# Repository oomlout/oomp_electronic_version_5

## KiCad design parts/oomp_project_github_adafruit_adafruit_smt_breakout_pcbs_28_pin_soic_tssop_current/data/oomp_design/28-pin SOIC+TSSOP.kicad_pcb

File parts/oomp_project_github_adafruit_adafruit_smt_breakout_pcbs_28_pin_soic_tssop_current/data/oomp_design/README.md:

# OOMP KiCad design copy

Open `28-pin SOIC+TSSOP.kicad_pro` (or the `.kicad_pcb` / `.kicad_sch`) in KiCad. Local OOMP libraries are under `libraries/`. Original inputs are preserved in [../original/](../original/).

Only verified unchanged installed KiCad defaults were renamed. Modified, custom, unmatched and unavailable items remain unchanged. Soldering variants are never swapped during conversion. Existing pad coordinates, nets and UUIDs are preserved.

See [conversion_report.yaml](conversion_report.yaml) for every conversion and skip. Copy this directory before editing; regeneration refuses to overwrite edited design files.

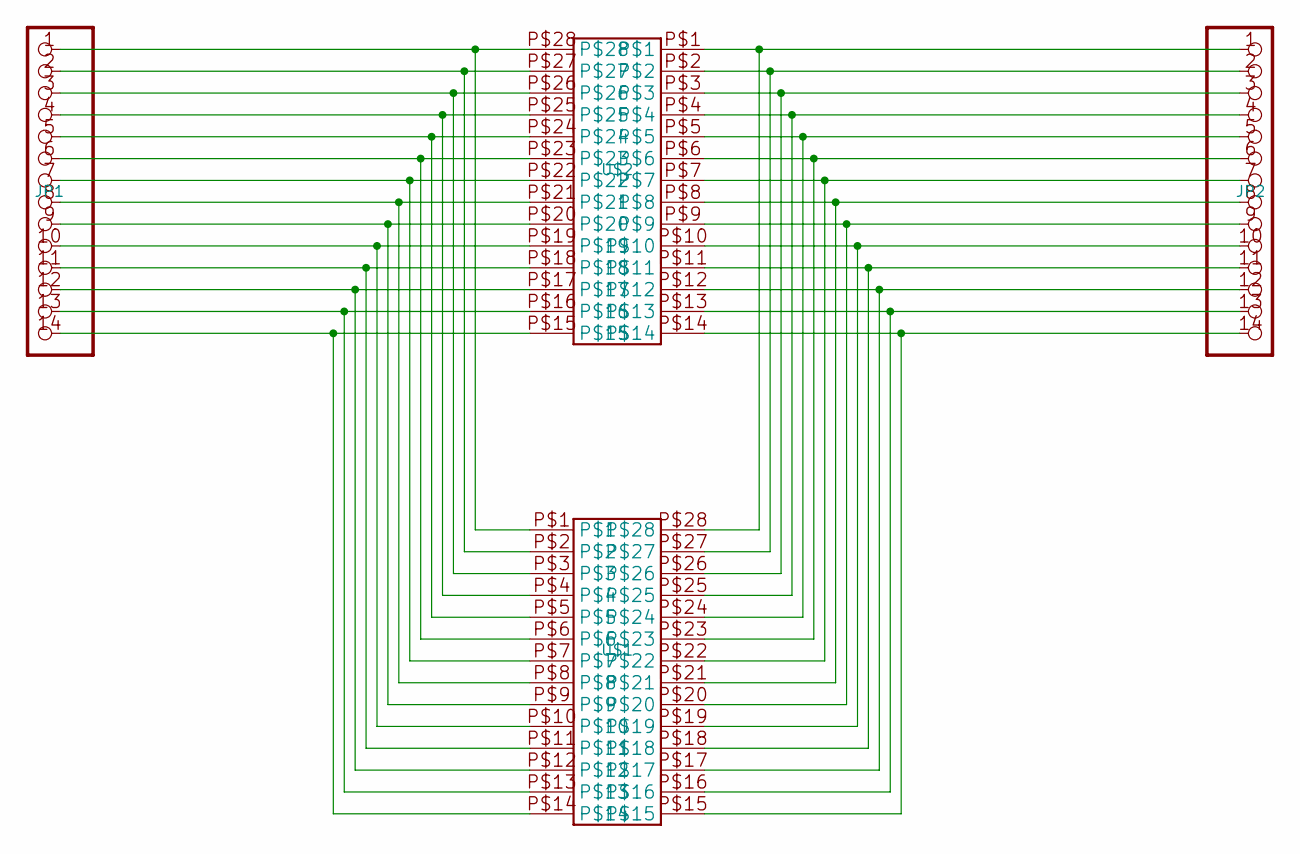
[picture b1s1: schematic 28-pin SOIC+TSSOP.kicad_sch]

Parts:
JP1, JP2: PADS-14
U$1: 28-PINSOIC-NW; SO28-NW
U$2: 28-PINTSSOP-NW; TSSOP28-NW

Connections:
unnamed: JP1.1, U$1.P$1, U$2.P$28
unnamed: JP1.2, U$1.P$2, U$2.P$27
unnamed: JP1.3, U$1.P$3, U$2.P$26
unnamed: JP1.4, U$1.P$4, U$2.P$25
unnamed: JP1.5, U$1.P$5, U$2.P$24
unnamed: JP1.6, U$1.P$6, U$2.P$23
unnamed: JP1.7, U$1.P$7, U$2.P$22
unnamed: JP1.8, U$1.P$8, U$2.P$21
unnamed: JP1.9, U$1.P$9, U$2.P$20
unnamed: JP1.10, U$1.P$10, U$2.P$19
unnamed: JP1.11, U$1.P$11, U$2.P$18
unnamed: JP1.12, U$1.P$12, U$2.P$17
unnamed: JP1.14, U$1.P$14, U$2.P$15
unnamed: JP2.1, U$1.P$28, U$2.P$1
unnamed: JP2.2, U$1.P$27, U$2.P$2
unnamed: JP2.3, U$1.P$26, U$2.P$3
unnamed: JP2.4, U$1.P$25, U$2.P$4
unnamed: JP2.5, U$1.P$24, U$2.P$5
unnamed: JP2.6, U$1.P$23, U$2.P$6
unnamed: JP2.7, U$1.P$22, U$2.P$7
unnamed: JP2.8, U$1.P$21, U$2.P$8
unnamed: JP2.9, U$1.P$20, U$2.P$9
unnamed: JP2.10, U$1.P$19, U$2.P$10
unnamed: JP2.11, U$1.P$18, U$2.P$11
unnamed: JP2.12, U$1.P$17, U$2.P$12
unnamed: JP2.13, U$1.P$16, U$2.P$13
unnamed: JP2.14, U$1.P$15, U$2.P$14
unnamed: JP1.13, U$1.P$13, U$2.P$16

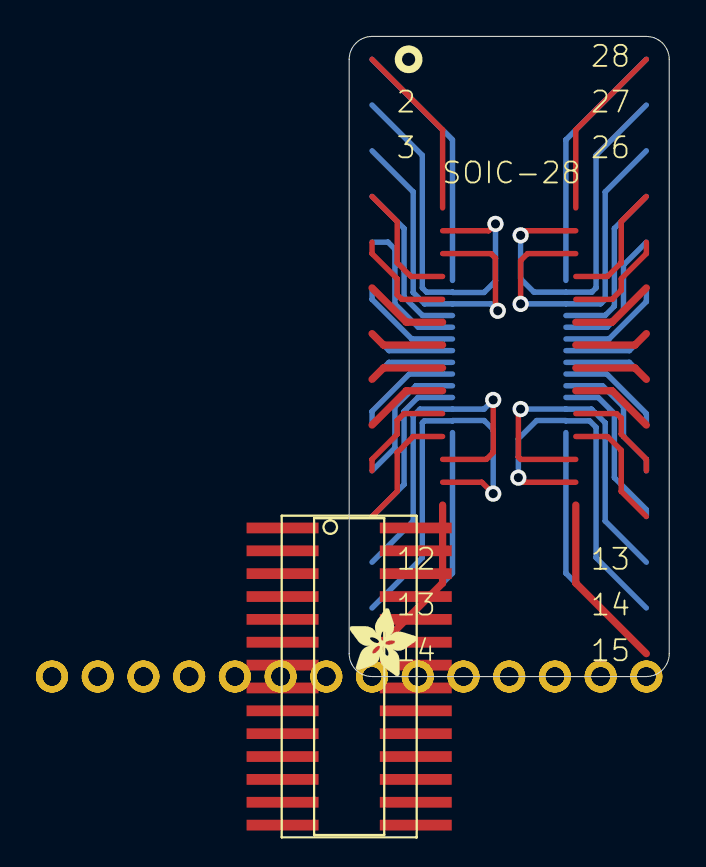
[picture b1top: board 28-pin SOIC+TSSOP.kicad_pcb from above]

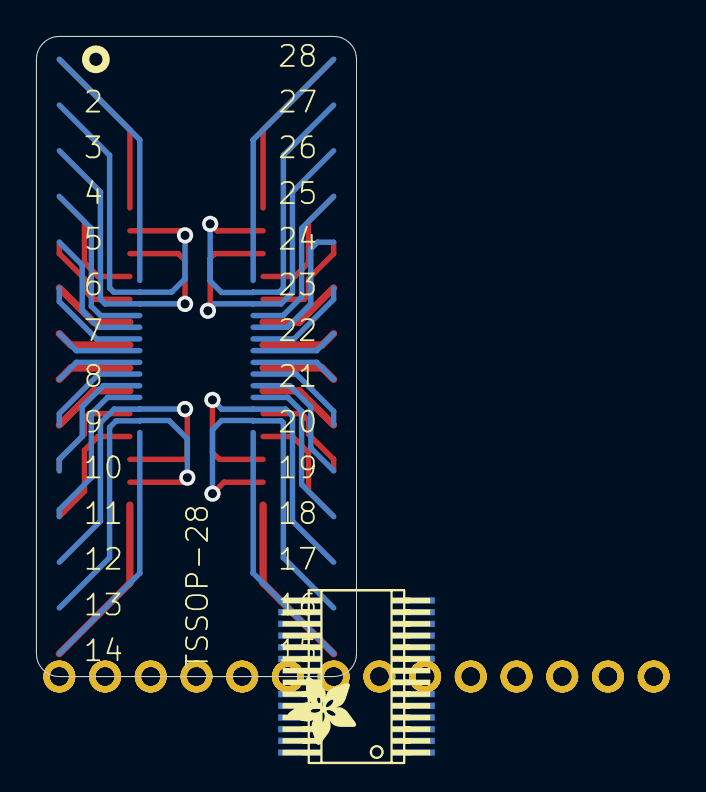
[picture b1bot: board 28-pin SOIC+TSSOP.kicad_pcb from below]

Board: 2 copper layers, 17.8 x 35.6 mm, 6 parts (2 on the bottom side), 28 nets.

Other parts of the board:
U$3, U$4: ADAFRUIT_3.5MM

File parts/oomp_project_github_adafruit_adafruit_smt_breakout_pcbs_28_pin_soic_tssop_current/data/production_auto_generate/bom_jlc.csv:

Comment,Designator,Footprint,LCSC Part #
,"U$3,U$4",28-pin SOIC+TSSOP-import-fps:ADAFRUIT_3.5MM,
,"JP1,JP2",28-pin SOIC+TSSOP-import-fps:PADS-14,
28-PINSOIC-NW,U$1,28-pin SOIC+TSSOP-import-fps:SO28-NW,
28-PINTSSOP-NW,U$2,28-pin SOIC+TSSOP-import-fps:TSSOP28-NW,

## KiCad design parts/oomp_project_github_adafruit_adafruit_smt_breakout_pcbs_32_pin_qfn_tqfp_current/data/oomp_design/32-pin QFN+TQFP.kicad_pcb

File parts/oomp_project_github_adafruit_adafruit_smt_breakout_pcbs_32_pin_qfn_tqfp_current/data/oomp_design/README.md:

# OOMP KiCad design copy

Open `32-pin QFN+TQFP.kicad_pro` (or the `.kicad_pcb` / `.kicad_sch`) in KiCad. Local OOMP libraries are under `libraries/`. Original inputs are preserved in [../original/](../original/).

Only verified unchanged installed KiCad defaults were renamed. Modified, custom, unmatched and unavailable items remain unchanged. Soldering variants are never swapped during conversion. Existing pad coordinates, nets and UUIDs are preserved.

See [conversion_report.yaml](conversion_report.yaml) for every conversion and skip. Copy this directory before editing; regeneration refuses to overwrite edited design files.

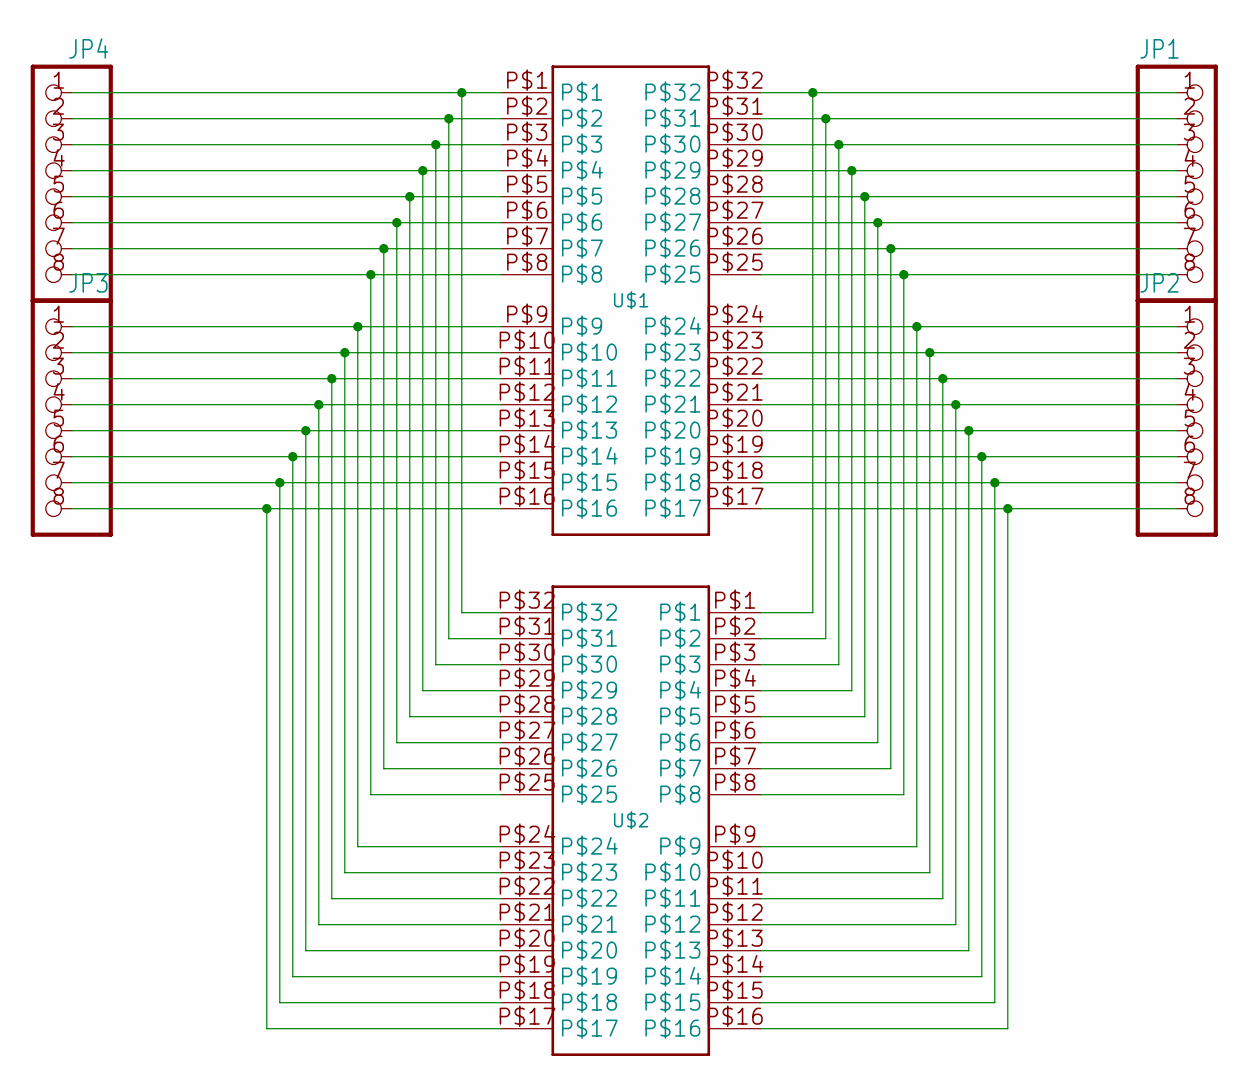
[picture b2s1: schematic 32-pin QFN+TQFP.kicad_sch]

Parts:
JP1, JP2, JP3, JP4: PADS-8CLEANBIG; PADS-8
U$1: 32-PINQFN; QFN32
U$2: 32-PINTQFP; TQFP32-08

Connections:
unnamed: JP4.1, U$1.P$1, U$2.P$32
unnamed: JP4.2, U$1.P$2, U$2.P$31
unnamed: JP4.3, U$1.P$3, U$2.P$30
unnamed: JP4.4, U$1.P$4, U$2.P$29
unnamed: JP4.5, U$1.P$5, U$2.P$28
unnamed: JP4.6, U$1.P$6, U$2.P$27
unnamed: JP4.7, U$1.P$7, U$2.P$26
unnamed: JP4.8, U$1.P$8, U$2.P$25
unnamed: JP3.1, U$1.P$9, U$2.P$24
unnamed: JP3.2, U$1.P$10, U$2.P$23
unnamed: JP3.3, U$1.P$11, U$2.P$22
unnamed: JP3.4, U$1.P$12, U$2.P$21
unnamed: JP3.5, U$1.P$13, U$2.P$20
unnamed: JP3.6, U$1.P$14, U$2.P$19
unnamed: JP3.7, U$1.P$15, U$2.P$18
unnamed: JP3.8, U$1.P$16, U$2.P$17
unnamed: JP1.1, U$1.P$32, U$2.P$1
unnamed: JP1.2, U$1.P$31, U$2.P$2
unnamed: JP1.3, U$1.P$30, U$2.P$3
unnamed: JP1.4, U$1.P$29, U$2.P$4
unnamed: JP1.5, U$1.P$28, U$2.P$5
unnamed: JP1.6, U$1.P$27, U$2.P$6
unnamed: JP1.7, U$1.P$26, U$2.P$7
unnamed: JP1.8, U$1.P$25, U$2.P$8
unnamed: JP2.1, U$1.P$24, U$2.P$9
unnamed: JP2.2, U$1.P$23, U$2.P$10
unnamed: JP2.3, U$1.P$22, U$2.P$11
unnamed: JP2.4, U$1.P$21, U$2.P$12
unnamed: JP2.5, U$1.P$20, U$2.P$13
unnamed: JP2.6, U$1.P$19, U$2.P$14
unnamed: JP2.7, U$1.P$18, U$2.P$15
unnamed: JP2.8, U$1.P$17, U$2.P$16

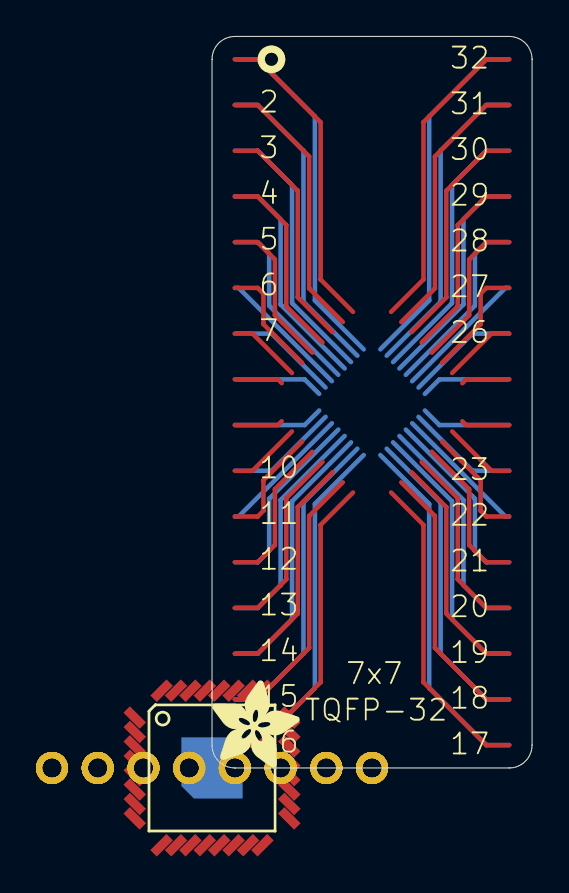
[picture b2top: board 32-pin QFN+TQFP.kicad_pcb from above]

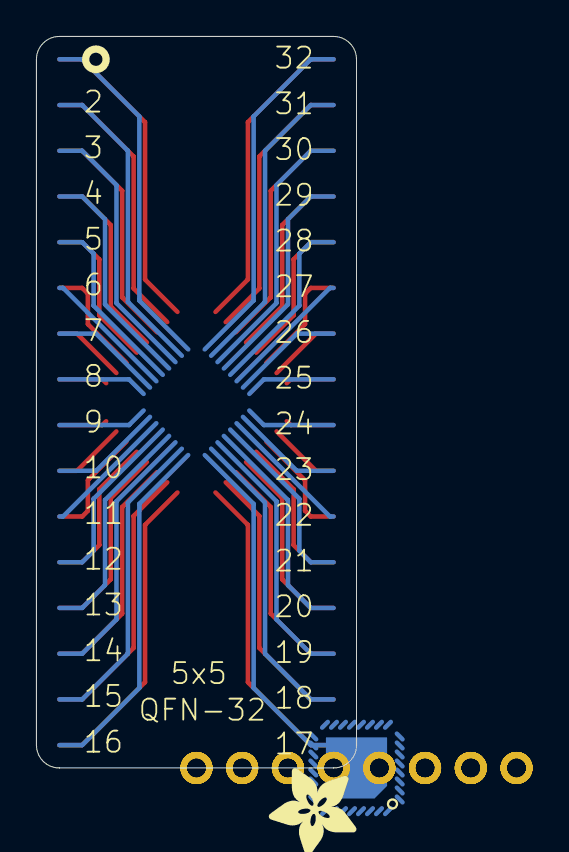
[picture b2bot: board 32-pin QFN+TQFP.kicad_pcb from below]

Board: 16 copper layers, 17.8 x 40.6 mm, 8 parts (2 on the bottom side), 32 nets.

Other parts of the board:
U$3, U$4: ADAFRUIT_5MM

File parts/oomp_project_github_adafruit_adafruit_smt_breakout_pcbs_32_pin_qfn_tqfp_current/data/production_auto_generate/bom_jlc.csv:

Comment,Designator,Footprint,LCSC Part #
,"U$3,U$4",32-pin QFN+TQFP-import-fps:ADAFRUIT_5MM,
,"JP1,JP2,JP3,JP4",32-pin QFN+TQFP-import-fps:PADS-8,
32-PINQFN,U$1,32-pin QFN+TQFP-import-fps:QFN32,
32-PINTQFP,U$2,32-pin QFN+TQFP-import-fps:TQFP32-08,

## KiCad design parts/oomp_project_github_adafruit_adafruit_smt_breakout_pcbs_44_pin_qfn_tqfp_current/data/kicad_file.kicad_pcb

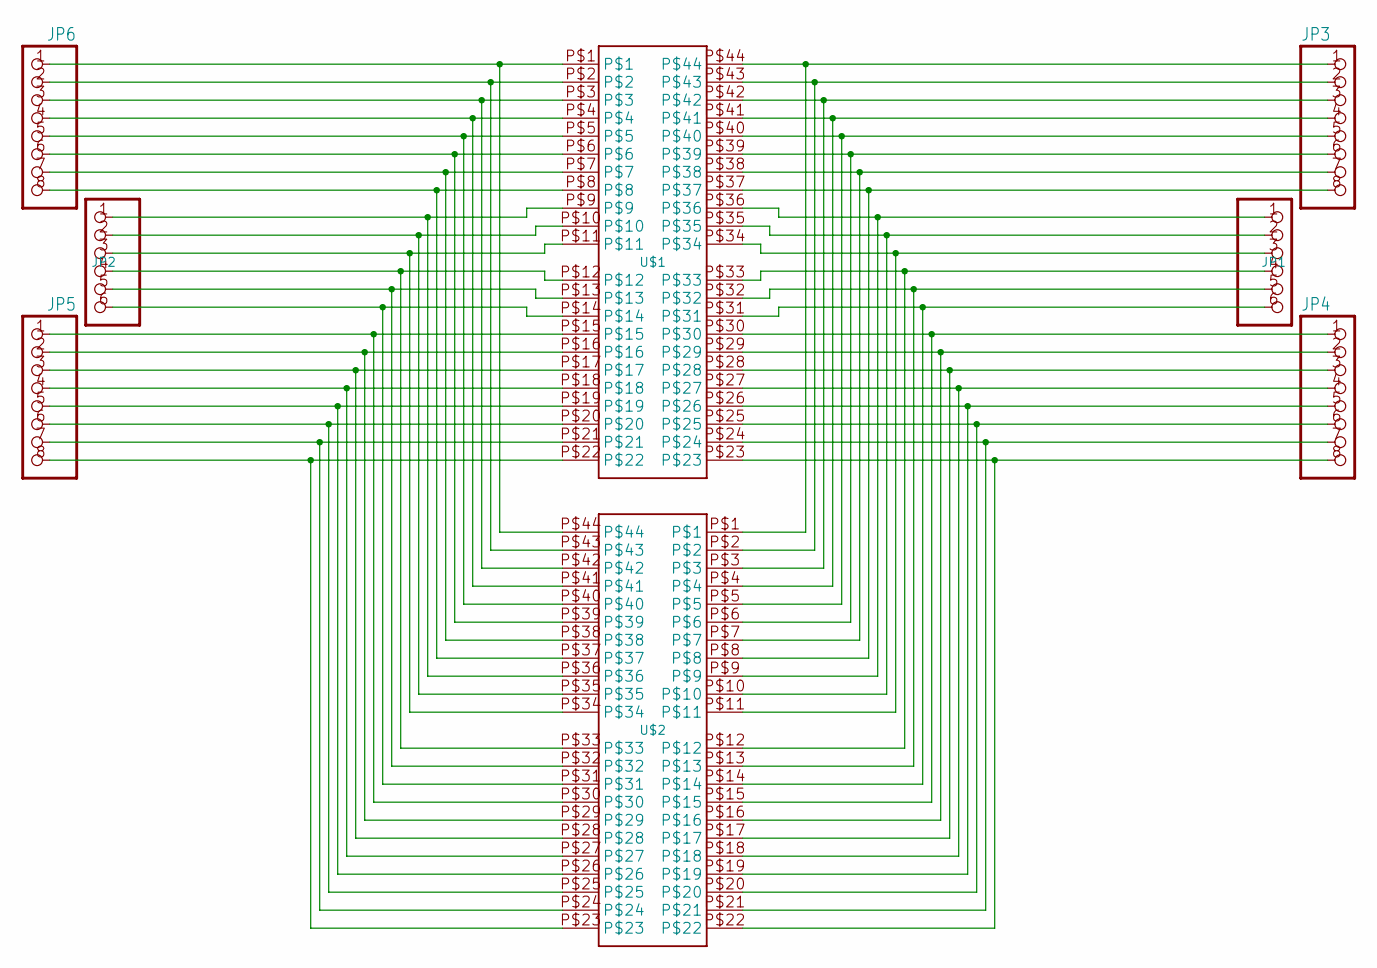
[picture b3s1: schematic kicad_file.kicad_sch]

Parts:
JP1, JP2: PADS-6
JP3, JP4, JP5, JP6: PADS-8CLEANBIG; PADS-8
U$1: 44-PINQFN; QFN44
U$2: 44-PINTQFP; TQFP44

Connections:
unnamed: JP6.1, U$1.P$1, U$2.P$44
unnamed: JP6.2, U$1.P$2, U$2.P$43
unnamed: JP6.3, U$1.P$3, U$2.P$42
unnamed: JP6.4, U$1.P$4, U$2.P$41
unnamed: JP6.5, U$1.P$5, U$2.P$40
unnamed: JP6.6, U$1.P$6, U$2.P$39
unnamed: JP6.7, U$1.P$7, U$2.P$38
unnamed: JP6.8, U$1.P$8, U$2.P$37
unnamed: JP5.1, U$1.P$15, U$2.P$30
unnamed: JP5.2, U$1.P$16, U$2.P$29
unnamed: JP5.3, U$1.P$17, U$2.P$28
unnamed: JP5.4, U$1.P$18, U$2.P$27
unnamed: JP5.5, U$1.P$19, U$2.P$26
unnamed: JP5.6, U$1.P$20, U$2.P$25
unnamed: JP5.7, U$1.P$21, U$2.P$24
unnamed: JP5.8, U$1.P$22, U$2.P$23
unnamed: JP4.1, U$1.P$30, U$2.P$15
unnamed: JP4.2, U$1.P$29, U$2.P$16
unnamed: JP4.3, U$1.P$28, U$2.P$17
unnamed: JP4.4, U$1.P$27, U$2.P$18
unnamed: JP4.5, U$1.P$26, U$2.P$19
unnamed: JP4.6, U$1.P$25, U$2.P$20
unnamed: JP4.7, U$1.P$24, U$2.P$21
unnamed: JP4.8, U$1.P$23, U$2.P$22
unnamed: JP3.1, U$1.P$44, U$2.P$1
unnamed: JP3.2, U$1.P$43, U$2.P$2
unnamed: JP3.3, U$1.P$42, U$2.P$3
unnamed: JP3.4, U$1.P$41, U$2.P$4
unnamed: JP3.5, U$1.P$40, U$2.P$5
unnamed: JP3.6, U$1.P$39, U$2.P$6
unnamed: JP3.7, U$1.P$38, U$2.P$7
unnamed: JP3.8, U$1.P$37, U$2.P$8
unnamed: JP1.4, U$1.P$33, U$2.P$12
unnamed: JP1.5, U$1.P$32, U$2.P$13
unnamed: JP1.6, U$1.P$31, U$2.P$14
unnamed: JP1.3, U$1.P$34, U$2.P$11
unnamed: JP1.2, U$1.P$35, U$2.P$10
unnamed: JP1.1, U$1.P$36, U$2.P$9
unnamed: JP2.3, U$1.P$11, U$2.P$34
unnamed: JP2.2, U$1.P$10, U$2.P$35
unnamed: JP2.1, U$1.P$9, U$2.P$36
unnamed: JP2.4, U$1.P$12, U$2.P$33
unnamed: JP2.5, U$1.P$13, U$2.P$32
unnamed: JP2.6, U$1.P$14, U$2.P$31

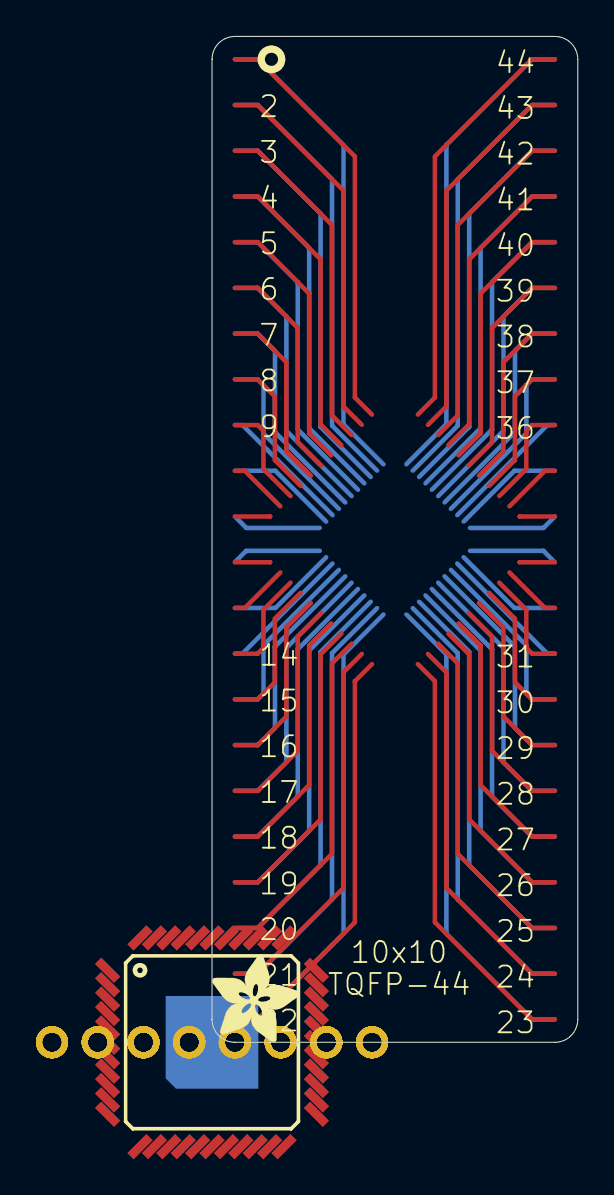
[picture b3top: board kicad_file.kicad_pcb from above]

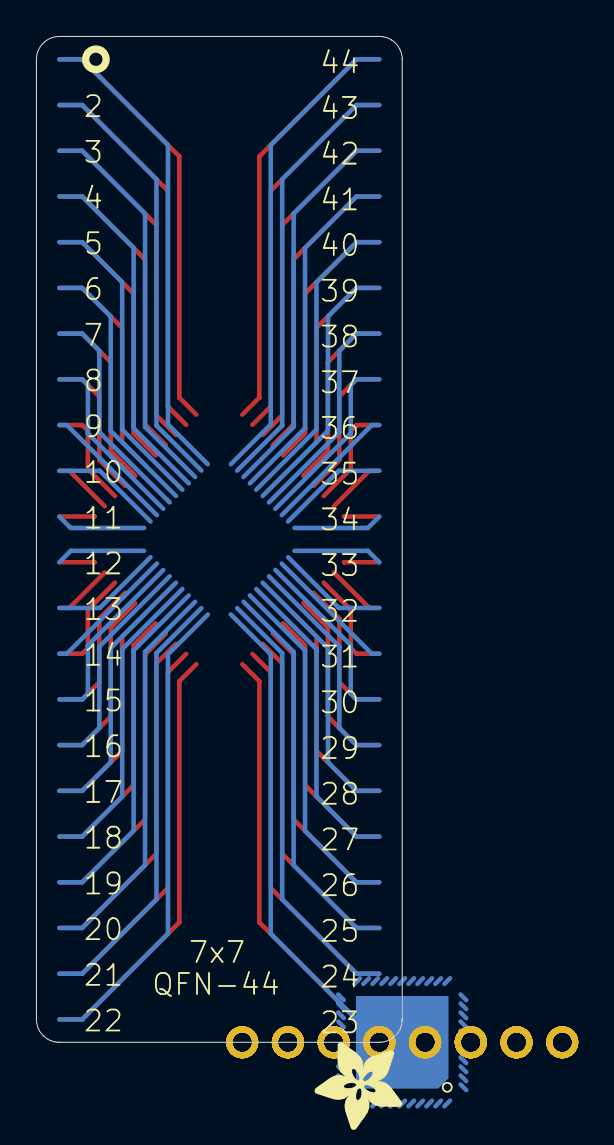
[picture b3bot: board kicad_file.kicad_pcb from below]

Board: 16 copper layers, 20.3 x 55.9 mm, 10 parts (2 on the bottom side), 44 nets.

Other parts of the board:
U$3, U$4: ADAFRUIT_5MM

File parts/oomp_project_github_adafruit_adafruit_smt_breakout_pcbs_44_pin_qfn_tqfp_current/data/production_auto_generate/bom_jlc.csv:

Comment,Designator,Footprint,LCSC Part #
,"U$3,U$4",44-pin QFN+TQFP-import-fps:ADAFRUIT_5MM,
,"JP1,JP2",44-pin QFN+TQFP-import-fps:PADS-6,
,"JP3,JP4,JP5,JP6",44-pin QFN+TQFP-import-fps:PADS-8,
44-PINQFN,U$1,44-pin QFN+TQFP-import-fps:QFN44,
44-PINTQFP,U$2,44-pin QFN+TQFP-import-fps:TQFP44,

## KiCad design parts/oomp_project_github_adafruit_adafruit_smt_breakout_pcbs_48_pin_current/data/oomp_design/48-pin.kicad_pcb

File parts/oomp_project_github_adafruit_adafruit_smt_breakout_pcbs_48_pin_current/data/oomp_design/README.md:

# OOMP KiCad design copy

Open `48-pin.kicad_pro` (or the `.kicad_pcb` / `.kicad_sch`) in KiCad. Local OOMP libraries are under `libraries/`. Original inputs are preserved in [../original/](../original/).

Only verified unchanged installed KiCad defaults were renamed. Modified, custom, unmatched and unavailable items remain unchanged. Soldering variants are never swapped during conversion. Existing pad coordinates, nets and UUIDs are preserved.

See [conversion_report.yaml](conversion_report.yaml) for every conversion and skip. Copy this directory before editing; regeneration refuses to overwrite edited design files.

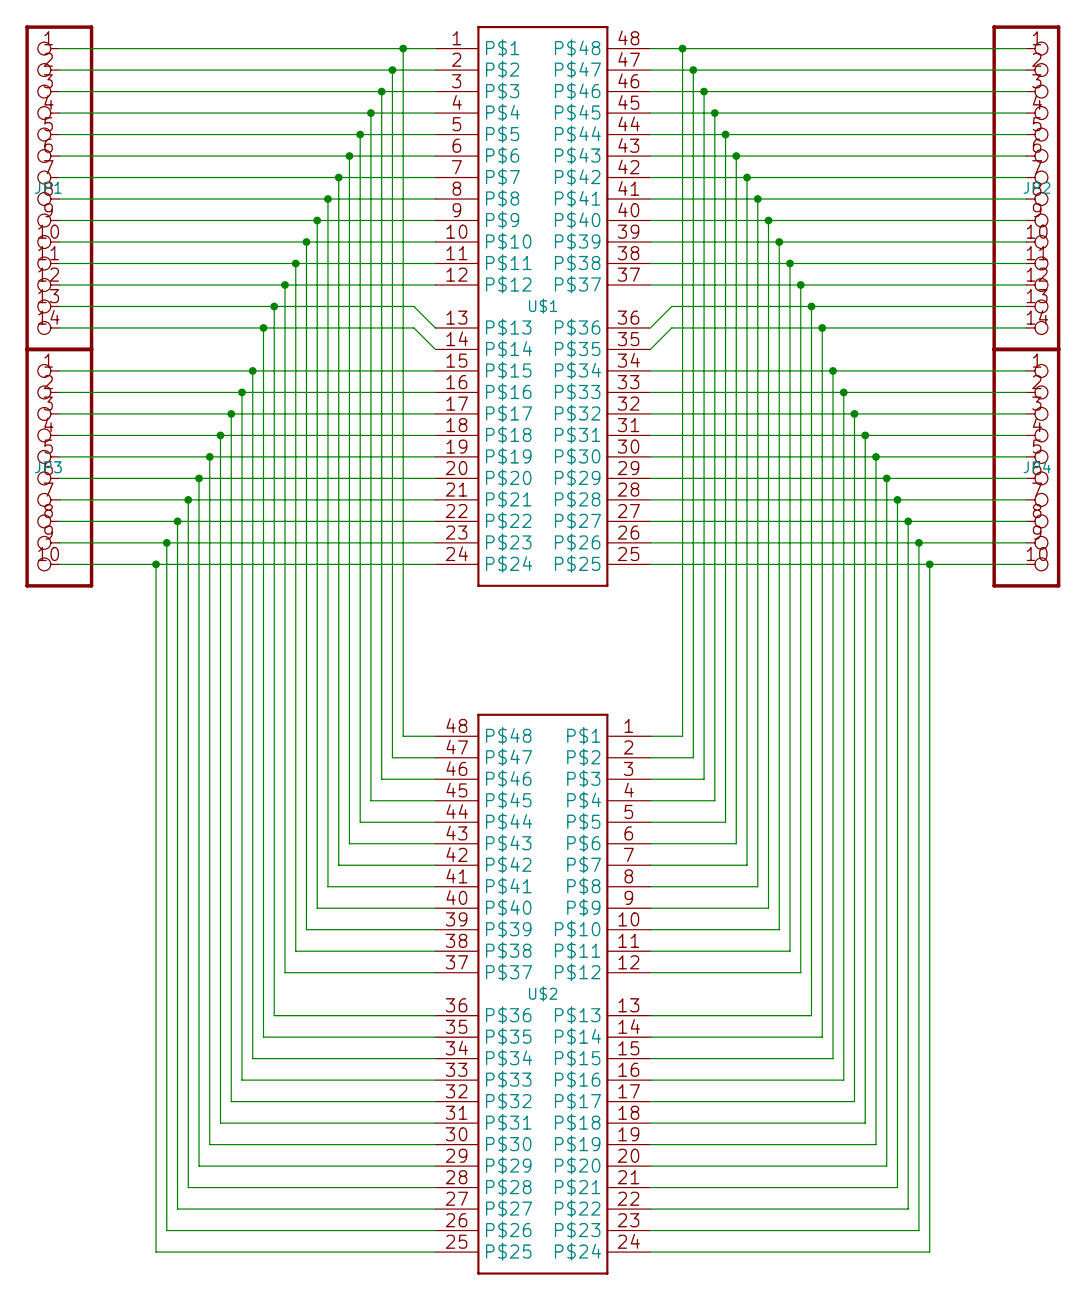
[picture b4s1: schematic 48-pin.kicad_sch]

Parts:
JP1, JP2: PADS-14
JP3, JP4: PADS-10
U$1: BREAKOUTS_48-PINTQFP; BREAKOUTS_TQFP48
U$2: BREAKOUTS_48-PINQFN; BREAKOUTS_QFN48

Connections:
.05: JP4.6, U$1.29, U$2.20
unnamed: JP1.1, U$1.1, U$2.48
unnamed: JP1.2, U$1.2, U$2.47
unnamed: JP1.3, U$1.3, U$2.46
unnamed: JP1.4, U$1.4, U$2.45
unnamed: JP1.5, U$1.5, U$2.44
unnamed: JP1.6, U$1.6, U$2.43
unnamed: JP1.7, U$1.7, U$2.42
unnamed: JP1.8, U$1.8, U$2.41
unnamed: JP1.9, U$1.9, U$2.40
unnamed: JP1.10, U$1.10, U$2.39
unnamed: JP1.11, U$1.11, U$2.38
unnamed: JP1.12, U$1.12, U$2.37
unnamed: JP3.1, U$1.15, U$2.34
unnamed: JP3.2, U$1.16, U$2.33
unnamed: JP3.3, U$1.17, U$2.32
unnamed: JP3.4, U$1.18, U$2.31
unnamed: JP3.5, U$1.19, U$2.30
unnamed: JP3.6, U$1.20, U$2.29
unnamed: JP3.7, U$1.21, U$2.28
unnamed: JP3.8, U$1.22, U$2.27
unnamed: JP3.9, U$1.23, U$2.26
unnamed: JP3.10, U$1.24, U$2.25
unnamed: JP2.1, U$1.48, U$2.1
unnamed: JP2.2, U$1.47, U$2.2
unnamed: JP2.3, U$1.46, U$2.3
unnamed: JP2.4, U$1.45, U$2.4
unnamed: JP2.5, U$1.44, U$2.5
unnamed: JP2.6, U$1.43, U$2.6
unnamed: JP2.7, U$1.42, U$2.7
unnamed: JP2.8, U$1.41, U$2.8
unnamed: JP2.10, U$1.39, U$2.10
unnamed: JP2.11, U$1.38, U$2.11
unnamed: JP2.12, U$1.37, U$2.12
unnamed: JP4.1, U$1.34, U$2.15
unnamed: JP4.2, U$1.33, U$2.16
unnamed: JP4.3, U$1.32, U$2.17
unnamed: JP4.4, U$1.31, U$2.18
unnamed: JP4.5, U$1.30, U$2.19
unnamed: JP4.7, U$1.28, U$2.21
unnamed: JP4.8, U$1.27, U$2.22
unnamed: JP4.9, U$1.26, U$2.23
unnamed: JP4.10, U$1.25, U$2.24
unnamed: JP1.14, U$1.14, U$2.35
unnamed: JP2.14, U$1.35, U$2.14
unnamed: JP2.13, U$1.36, U$2.13
unnamed: JP1.13, U$1.13, U$2.36
unnamed: JP2.9, U$1.40, U$2.9

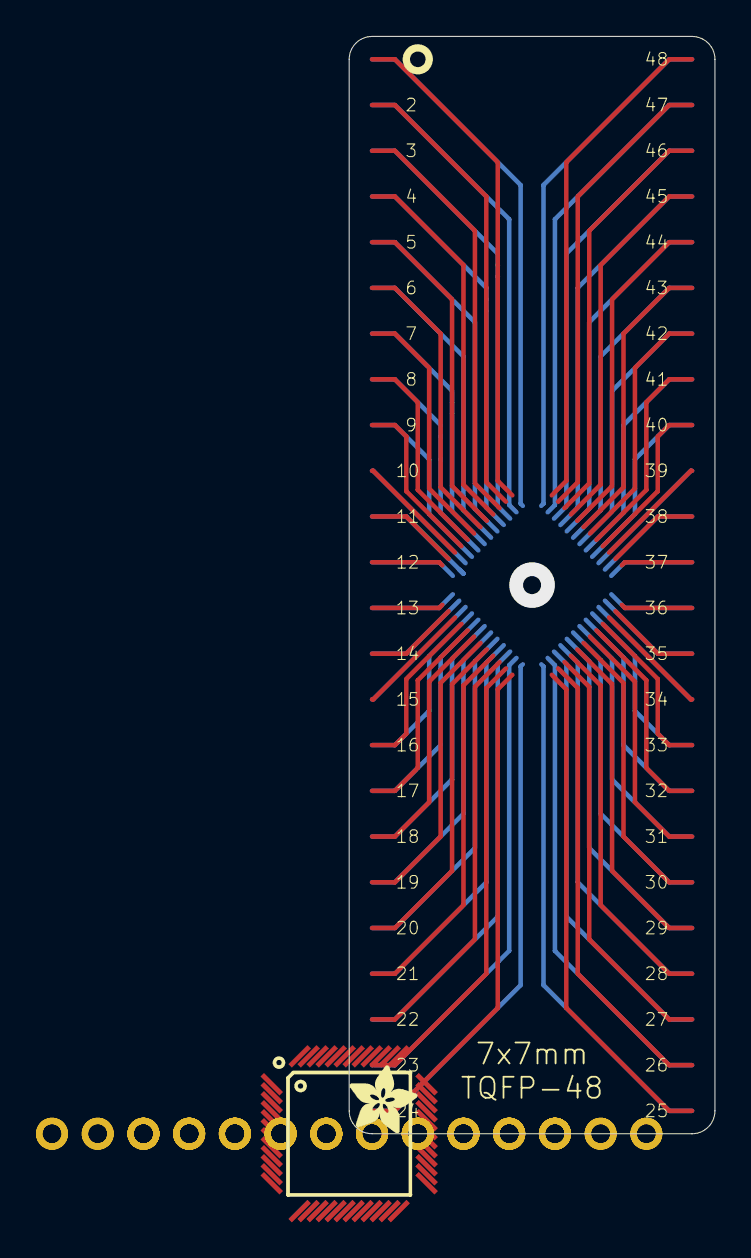
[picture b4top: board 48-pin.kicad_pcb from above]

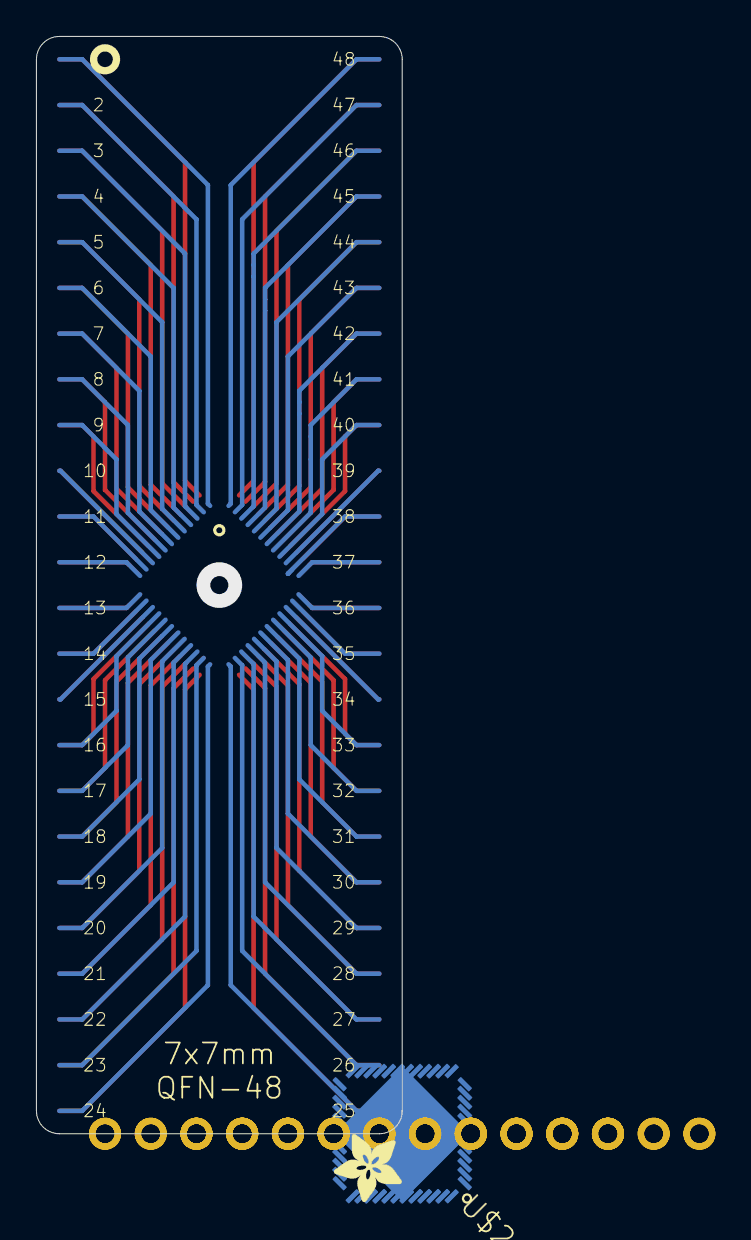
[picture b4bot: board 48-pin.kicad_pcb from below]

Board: 2 copper layers, 20.3 x 61.0 mm, 8 parts (2 on the bottom side), 48 nets.

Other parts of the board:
U$3, U$4: ADAFRUIT_3.5MM

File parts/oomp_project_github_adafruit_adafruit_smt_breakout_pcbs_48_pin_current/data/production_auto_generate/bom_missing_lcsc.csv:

Designator,Comment,Footprint,OOMP ID,Reason
JP1,,48-pin-import-fps:PADS-14,,No verified LCSC part number
JP2,,48-pin-import-fps:PADS-14,,No verified LCSC part number
JP3,,48-pin-import-fps:PADS-10,,No verified LCSC part number
JP4,,48-pin-import-fps:PADS-10,,No verified LCSC part number
U$1,BREAKOUTS_48-PINTQFP,48-pin-import-fps:BREAKOUTS_TQFP48,,No verified LCSC part number
U$2,BREAKOUTS_48-PINQFN,48-pin-import-fps:BREAKOUTS_QFN48,,No verified LCSC part number
U$3,,48-pin-import-fps:ADAFRUIT_3.5MM,,No verified LCSC part number
U$4,,48-pin-import-fps:ADAFRUIT_3.5MM,,No verified LCSC part number
